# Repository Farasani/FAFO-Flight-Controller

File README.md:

# FAFO

<picture>
  <source media="(prefers-color-scheme: dark)" width=60% height=60% srcset="https://github.com/user-attachments/assets/f2668aae-5746-43aa-aec3-286b064c4626">
  <source media="(prefers-color-scheme: light)" width=60% height=60% srcset="https://github.com/user-attachments/assets/a5b0ae70-b65e-41dd-a281-93c37e5f3b0a">
  
</picture>

F4 Flight Controller for quadcopter, hecxacopter and fixed wings drones.

## Specs

- 168MHz STM32F405RGT6
- 5x UARTS serial ports
- I2C1
- 6-Axis ICM-42688-P
- MAX7456 OSD
- BMP280 Barometer
- 1GB BlackBox
- 6 PWM/DSHOT outputs

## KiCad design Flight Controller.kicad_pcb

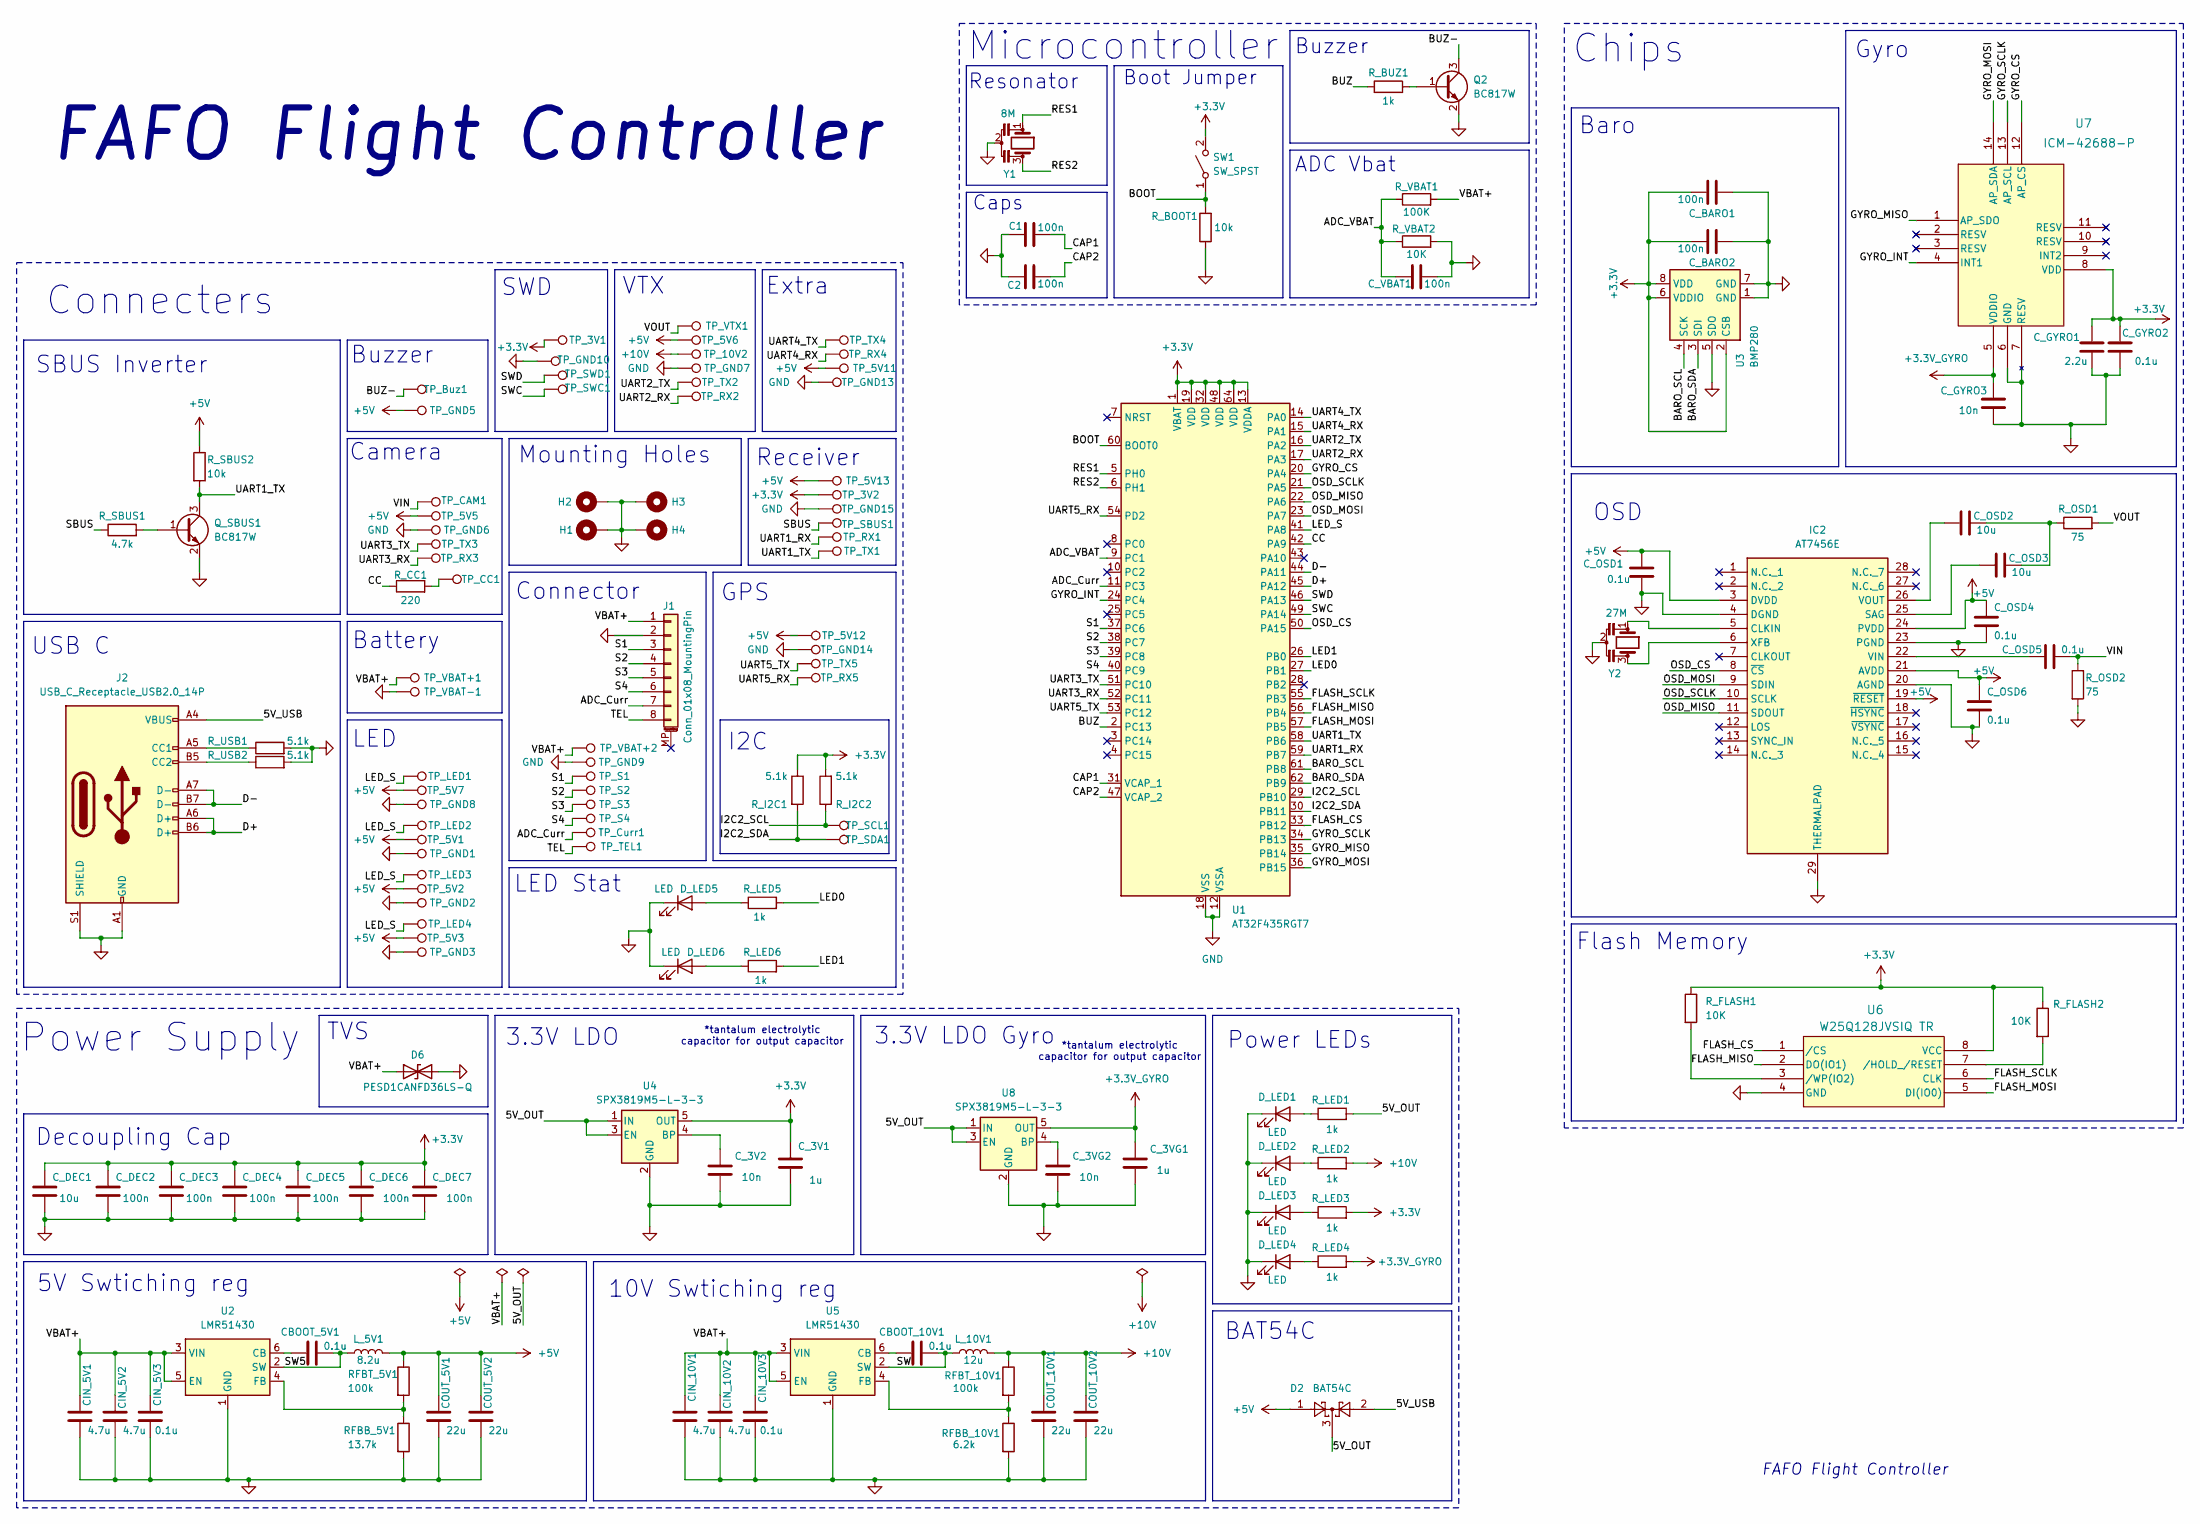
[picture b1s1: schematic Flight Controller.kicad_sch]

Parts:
C1, C2: 100n; C_0402_1005Metric
CBOOT_5V1, CBOOT_10V1: 0.1u; C_0603_1608Metric
CIN_5V1, CIN_5V2, CIN_10V1, CIN_10V2: 4.7u; C_0805_2012Metric
CIN_5V3, CIN_10V3: 0.1u; C_0402_1005Metric
COUT_5V1, COUT_5V2, COUT_10V1, COUT_10V2: 22u; C_0805_2012Metric
C_3V1, C_3VG1: 1u; C_0603_1608Metric
C_3V2, C_3VG2: 10n; C_0402_1005Metric
C_BARO1, C_BARO2: 100n; C_0402_1005Metric
C_DEC1: 10u; C_0603_1608Metric
C_DEC2, C_DEC3, C_DEC4, C_DEC5, C_DEC6, C_DEC7: 100n; C_0402_1005Metric
C_GYRO1: 2.2u; C_0402_1005Metric
C_GYRO2: 0.1u; C_0402_1005Metric
C_GYRO3: 10n; C_0402_1005Metric
C_OSD1, C_OSD4, C_OSD5, C_OSD6: 0.1u; C_0402_1005Metric
C_OSD2, C_OSD3: 10u; C_0402_1005Metric
C_VBAT1: 100n; C_0402_1005Metric
D2: BAT54C; SOT-23
D6: PESD1CANFD36LS-Q; D_SOD-882
D_LED1, D_LED2, D_LED3, D_LED4, D_LED5, D_LED6: LED; LED_0603_1608Metric
H1, H2, H3, H4: MountingHole_Pad; MountingHole_3.2mm_M3_DIN965_Pad
IC2: AT7456E; SOP65P637X110-28N; Manufacturer_Part_Number AT7456E
J1: Conn_01x08_MountingPin; JST_SH_SM08B-SRSS-TB_1x08-1MP_P1.00mm_Horizontal
J2: USB_C_Receptacle_USB2.0_14P; USB_C_Receptacle_GCT_USB4110
L_5V1: 8.2u; L_Vishay_IHLP-2525
L_10V1: 12u; 744393465120
Q2: BC817W; SOT-323_SC-70
Q_SBUS1: BC817W; SOT-323_SC-70
RFBB_5V1: 13.7k; R_0402_1005Metric
RFBB_10V1: 6.2k; R_0402_1005Metric
RFBT_5V1, RFBT_10V1: 100k; R_0402_1005Metric
R_BOOT1: 10k; R_0402_1005Metric
R_BUZ1: 1k; R_0402_1005Metric
R_CC1: 220; R_0402_1005Metric
R_FLASH1, R_FLASH2: 10K; R_0402_1005Metric
R_I2C1, R_I2C2: 5.1k; R_0402_1005Metric
R_LED1, R_LED2, R_LED3, R_LED4, R_LED5, R_LED6: 1k; R_0603_1608Metric
R_OSD1, R_OSD2: 75; R_0603_1608Metric
R_SBUS1: 4.7k; R_0805_2012Metric
R_SBUS2: 10k; R_0603_1608Metric
R_USB1, R_USB2: 5.1k; R_0603_1608Metric
R_VBAT1: 100K; R_0805_2012Metric
R_VBAT2: 10K; R_1206_3216Metric
SW1: SW_SPST; SW_SPST_EVQP2_MiddlePushTravel_H2.5mm
TP_3V1, TP_3V2, TP_5V1, TP_5V2, TP_5V3, TP_5V5, TP_5V6, TP_5V7, TP_5V11, TP_5V12, TP_5V13, TP_10V2: TestPoint; Solder_Pad_SMD
TP_Buz1: TestPoint; Solder_Pad_SMD
TP_CAM1: TestPoint; Solder_Pad_SMD
TP_CC1: TestPoint; Solder_Pad_SMD
TP_Curr1: TestPoint; Solder_Pad_SMD_Half
TP_GND1, TP_GND2, TP_GND3, TP_GND5, TP_GND6, TP_GND7, TP_GND8, TP_GND10, TP_GND13, TP_GND14, TP_GND15: TestPoint; Solder_Pad_SMD
TP_GND9: TestPoint; Solder_Pad_SMD_Half
TP_LED1, TP_LED2, TP_LED3, TP_LED4: TestPoint; Solder_Pad_SMD
TP_RX1, TP_RX2, TP_RX3, TP_RX4, TP_RX5: TestPoint; Solder_Pad_SMD
TP_S1, TP_S2, TP_S3, TP_S4: TestPoint; Solder_Pad_SMD_Half
TP_SBUS1: TestPoint; Solder_Pad_SMD
TP_SCL1: TestPoint; Solder_Pad_SMD
TP_SDA1: TestPoint; Solder_Pad_SMD
TP_SWC1: TestPoint; Solder_Pad_SMD
TP_SWD1: TestPoint; Solder_Pad_SMD
TP_TEL1: TestPoint; Solder_Pad_SMD_Half
TP_TX1, TP_TX2, TP_TX3, TP_TX4, TP_TX5: TestPoint; Solder_Pad_SMD
TP_VBAT+1: TestPoint; Solder_Pad_SMD
TP_VBAT+2: TestPoint; Solder_Pad_SMD_Half
TP_VBAT-1: TestPoint; Solder_Pad_SMD
TP_VTX1: TestPoint; Solder_Pad_SMD
U1: AT32F435RGT7; LQFP-64_10x10mm_P0.5mm
U2, U5: LMR51430; SOT-23-6
U3: BMP280; Bosch_LGA-8_2x2.5mm_P0.65mm_ClockwisePinNumbering
U4, U8: SPX3819M5-L-3-3; SOT-23-5
U6: W25Q128JVSIQ TR; SOIC_208MIL_WIN
U7: ICM-42688-P; Bosch_LGA-14_3x2.5mm_P0.5mm
Y1: 8M; Resonator_SMD_Murata_CSTxExxV-3Pin_3.0x1.1mm
Y2: 27M; E2X270061X04

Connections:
+3.3V: C_3V1.1, C_BARO1.2, C_BARO2.2, C_DEC1.1, C_DEC2.1, C_DEC3.1, C_DEC4.1, C_DEC5.1, C_DEC6.1, C_DEC7.1, C_GYRO1.1, C_GYRO2.1, R_FLASH1.1, R_FLASH2.1, R_I2C1.1, R_I2C2.2, R_LED3.2, SW1.2 (B), TP_3V1.1, TP_3V2.1, U1.1 (VBAT), U1.13 (VDDA), U1.19 (VDD), U1.32 (VDD), U1.48 (VDD), U1.64 (VDD), U3.2 (CSB), U3.6 (VDDIO), U3.8 (VDD), U4.5 (OUT), U6.8 (VCC), U7.8 (VDD)
+3.3V_GYRO: C_3VG1.1, C_GYRO3.1, R_LED4.2, U7.5 (VDDIO), U8.5 (OUT)
+5V: COUT_5V1.1, COUT_5V2.1, C_OSD1.1, C_OSD4.1, C_OSD6.1, D2.1, IC2.3 (DVDD), IC2.19 (~RESET), IC2.21 (AVDD), IC2.24 (PVDD), L_5V1.2, RFBT_5V1.1, R_SBUS2.1, TP_5V1.1, TP_5V2.1, TP_5V3.1, TP_5V5.1, TP_5V6.1, TP_5V7.1, TP_5V11.1, TP_5V12.1, TP_5V13.1, TP_GND5.1
+10V: COUT_10V1.1, COUT_10V2.1, L_10V1.2, RFBT_10V1.1, R_LED2.2, TP_10V2.1
/5V_OUT: D2.3, R_LED1.2, U4.1 (IN), U4.3 (EN), U8.1 (IN), U8.3 (EN)
/5V_USB: D2.2, J2.A4 (VBUS), J2.A9 (VBUS), J2.B4 (VBUS), J2.B9 (VBUS)
/ADC_Curr: J1.7, TP_Curr1.1, U1.11 (PC3)
/ADC_VBAT: C_VBAT1.2, R_VBAT1.1, R_VBAT2.1, U1.9 (PC1)
/BARO_SCL: U1.61 (PB8), U3.4 (SCK)
/BARO_SDA: U1.62 (PB9), U3.3 (SDI)
/BOOT: R_BOOT1.2, SW1.1 (A), U1.60 (BOOT0)
/BUZ: R_BUZ1.1, U1.2 (PC13)
/BUZ-: Q2.3 (C), TP_Buz1.1
/CAP1: C1.2, U1.31 (VCAP_1)
/CAP2: C2.2, U1.47 (VCAP_2)
/CC: R_CC1.1, U1.42 (PA9)
/D+: J2.A6 (D+), J2.B6 (D+), U1.45 (PA12)
/D-: J2.A7 (D-), J2.B7 (D-), U1.44 (PA11)
/FLASH_CS: U1.33 (PB12), U6.1 (/CS)
/FLASH_MISO: U1.56 (PB4), U6.2 (DO(IO1))
/FLASH_MOSI: U1.57 (PB5), U6.5 (DI(IO0))
/FLASH_SCLK: U1.55 (PB3), U6.6 (CLK)
/GYRO_CS: U1.20 (PA4), U7.12 (AP_CS)
/GYRO_INT: U1.24 (PC4), U7.4 (INT1)
/GYRO_MISO: U1.35 (PB14), U7.1 (AP_SDO)
/GYRO_MOSI: U1.36 (PB15), U7.14 (AP_SDA)
/GYRO_SCLK: U1.34 (PB13), U7.13 (AP_SCL)
/I2C2_SCL: R_I2C2.1, TP_SCL1.1, U1.29 (PB10)
/I2C2_SDA: R_I2C1.2, TP_SDA1.1, U1.30 (PB11)
/LED0: R_LED5.2, U1.27 (PB1)
/LED1: R_LED6.2, U1.26 (PB0)
/LED_S: TP_LED1.1, TP_LED2.1, TP_LED3.1, TP_LED4.1, U1.41 (PA8)
/OSD_CS: IC2.8 (~CS), U1.50 (PA15)
/OSD_MISO: IC2.11 (SDOUT), U1.22 (PA6)
/OSD_MOSI: IC2.9 (SDIN), U1.23 (PA7)
/OSD_SCLK: IC2.10 (SCLK), U1.21 (PA5)
/RES1: U1.5 (PH0), Y1.1
/RES2: U1.6 (PH1), Y1.3
/S1: J1.3, TP_S1.1, U1.37 (PC6)
/S2: J1.4, TP_S2.1, U1.38 (PC7)
/S3: J1.5, TP_S3.1, U1.39 (PC8)
/S4: J1.6, TP_S4.1, U1.40 (PC9)
/SBUS: R_SBUS1.1, TP_SBUS1.1
/SW: CBOOT_10V1.2, L_10V1.1, U5.2 (SW)
/SW5: CBOOT_5V1.2, L_5V1.1, U2.2 (SW)
/SWC: TP_SWC1.1, U1.49 (PA14)
/SWD: TP_SWD1.1, U1.46 (PA13)
/TEL: J1.8, TP_TEL1.1
/UART1_RX: TP_RX1.1, U1.59 (PB7)
/UART1_TX: Q_SBUS1.3 (C), R_SBUS2.2, TP_TX1.1, U1.58 (PB6)
/UART2_RX: TP_RX2.1, U1.17 (PA3)
/UART2_TX: TP_TX2.1, U1.16 (PA2)
/UART3_RX: TP_RX3.1, U1.52 (PC11)
/UART3_TX: TP_TX3.1, U1.51 (PC10)
/UART4_RX: TP_RX4.1, U1.15 (PA1)
/UART4_TX: TP_TX4.1, U1.14 (PA0)
/UART5_RX: TP_RX5.1, U1.54 (PD2)
/UART5_TX: TP_TX5.1, U1.53 (PC12)
/VBAT+: CIN_5V1.1, CIN_5V2.1, CIN_5V3.2, CIN_10V1.1, CIN_10V2.1, CIN_10V3.2, D6.1 (A1), J1.1, R_VBAT1.2, TP_VBAT+1.1, TP_VBAT+2.1, U2.3 (VIN), U2.5 (EN), U5.3 (VIN), U5.5 (EN)
/VIN: C_OSD5.2, R_OSD2.1, TP_CAM1.1
/VOUT: R_OSD1.2, TP_VTX1.1
GND: C1.1, C2.1, CIN_5V1.2, CIN_5V2.2, CIN_5V3.1, CIN_10V1.2, CIN_10V2.2, CIN_10V3.1, COUT_5V1.2, COUT_5V2.2, COUT_10V1.2, COUT_10V2.2, C_3V1.2, C_3V2.2, C_3VG1.2, C_3VG2.2, C_BARO1.1, C_BARO2.1, C_DEC1.2, C_DEC2.2, C_DEC3.2, C_DEC4.2, C_DEC5.2, C_DEC6.2, C_DEC7.2, C_GYRO1.2, C_GYRO2.2, C_GYRO3.2, C_OSD1.2, C_OSD4.2, C_OSD6.2, C_VBAT1.1, D6.2 (A2), D_LED1.1 (K), D_LED2.1 (K), D_LED3.1 (K), D_LED4.1 (K), D_LED5.1 (K), D_LED6.1 (K), H1.1, H2.1, H3.1, H4.1, IC2.4 (DGND), IC2.20 (AGND), IC2.23 (PGND), IC2.29 (THERMALPAD), J1.2, J2.A1 (GND), J2.A12 (GND), J2.B1 (GND), J2.B12 (GND), J2.S1 (SHIELD), Q2.2 (E), Q_SBUS1.2 (E), RFBB_5V1.2, RFBB_10V1.2, R_BOOT1.1, R_OSD2.2, R_USB1.2, R_USB2.2, R_VBAT2.2, TP_GND1.1, TP_GND2.1, TP_GND3.1, TP_GND6.1, TP_GND7.1, TP_GND8.1, TP_GND9.1, TP_GND10.1, TP_GND13.1, TP_GND14.1, TP_GND15.1, TP_VBAT-1.1, U1.12 (VSSA), U1.18 (VSS), U1.63 (VSS), U2.1 (GND), U3.1 (GND), U3.5 (SDO), U3.7 (GND), U4.2 (GND), U5.1 (GND), U6.4 (GND), U7.6 (GND), U7.7 (RESV), U8.2 (GND), Y1.2, Y2.2
unnamed: C_OSD2.2, C_OSD3.2, R_OSD1.1
unnamed: D_LED1.2 (A), R_LED1.1
unnamed: D_LED2.2 (A), R_LED2.1
unnamed: D_LED3.2 (A), R_LED3.1
unnamed: D_LED4.2 (A), R_LED4.1
unnamed: D_LED5.2 (A), R_LED5.1
unnamed: D_LED6.2 (A), R_LED6.1
unnamed: IC2.5 (CLKIN), Y2.1
unnamed: C_OSD3.1, IC2.25 (SAG)
unnamed: C_OSD5.1, IC2.22 (VIN)
unnamed: C_OSD2.1, IC2.26 (VOUT)
unnamed: IC2.6 (XFB), Y2.3
unnamed: J2.A5 (CC1), R_USB1.1
unnamed: J2.B5 (CC2), R_USB2.1
unnamed: Q2.1 (B), R_BUZ1.2
unnamed: Q_SBUS1.1 (B), R_SBUS1.2
unnamed: R_CC1.2, TP_CC1.1
unnamed: CBOOT_5V1.1, U2.6 (CB)
unnamed: RFBB_5V1.1, RFBT_5V1.2, U2.4 (FB)
unnamed: C_3V2.1, U4.4 (BP)
unnamed: CBOOT_10V1.1, U5.6 (CB)
unnamed: RFBB_10V1.1, RFBT_10V1.2, U5.4 (FB)
unnamed: R_FLASH2.2, U6.7 (/HOLD_/RESET)
unnamed: R_FLASH1.2, U6.3 (/WP(IO2))
unnamed: C_3VG2.1, U8.4 (BP)

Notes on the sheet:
LED
Receiver
SBUS Inverter
Buzzer
Extra
FAFO Flight Controller
Battery
SWD
*tantalum electrolytic capacitor for output capacitor
Resonator
Decoupling Cap
Mounting Holes
3.3V LDO Gyro
Camera
Baro
Gyro
3.3V LDO
Caps
Microcontroller
Flash Memory
GPS
USB C
10V Swtiching reg
I2C
TVS
Power LEDs
Connector
BAT54C
VTX
Power Supply
Boot Jumper
LED Stat
ADC Vbat
5V Swtiching reg
OSD
Connecters
Chips

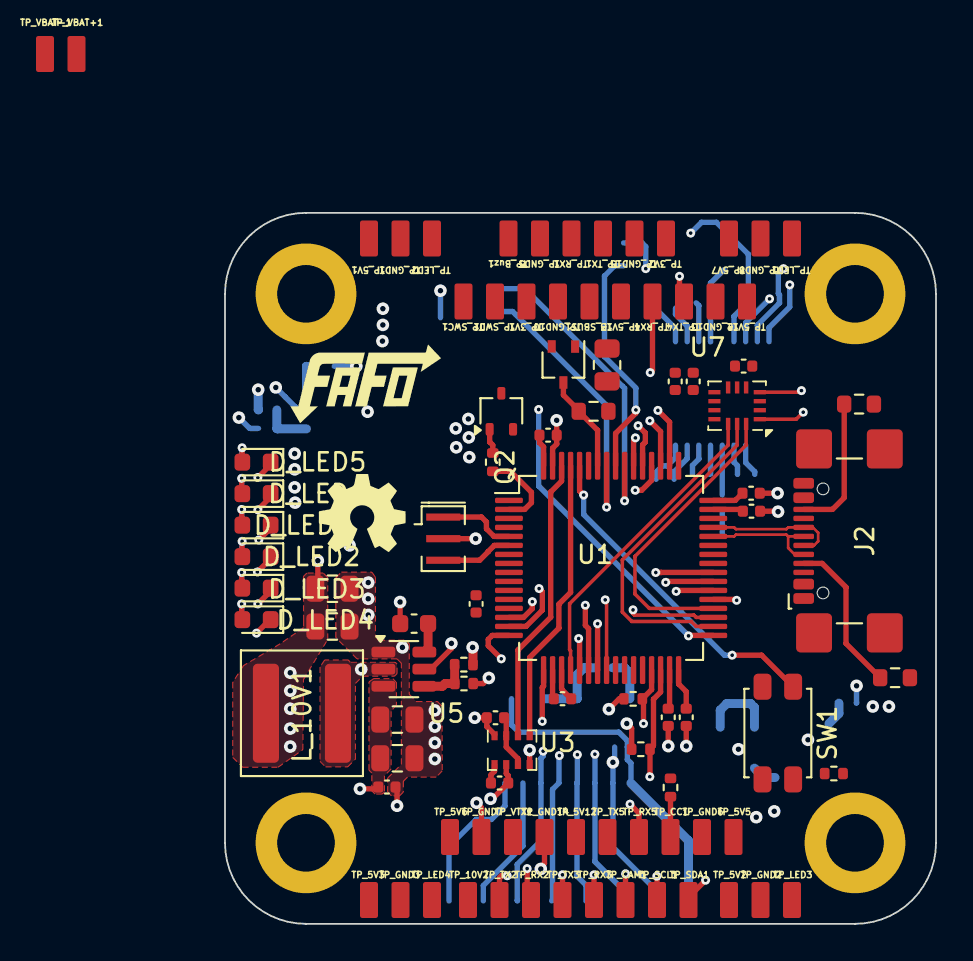
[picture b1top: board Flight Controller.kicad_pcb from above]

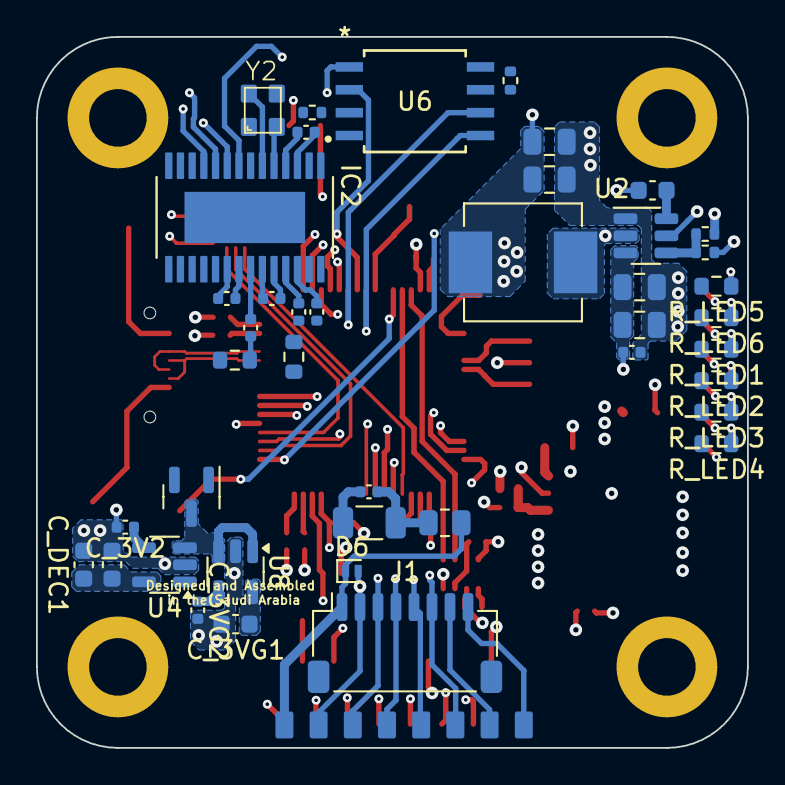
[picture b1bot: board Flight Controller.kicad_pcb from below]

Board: 6 copper layers, 39.5 x 39.5 mm, 147 parts (50 on the bottom side), 87 nets.

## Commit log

2024-04-01 added Kicad files
2024-04-08 schematic update
2024-04-08 pdf upload
2024-04-16 Update Schematic
2024-08-04 Updated Schematics
2025-01-04 Finshed Schematics and started with layout
2025-08-17 Readme
2025-08-21 Layout Update
2025-08-25 Power Supply Sch Udpate
2025-08-30 Changes to compline with Betaflighe guidlines
2025-09-08 assgining new pins
2025-09-09 Power Supply Updates
2025-09-10 New connectors
2025-09-18 I hope I'm done here with the sch
2025-09-18 This time I'm done fr
2025-09-18 I'm losing it
2025-09-19 Updated naming system
2025-09-19 I'm losing it again
2025-09-20 AHHHHHHHHHHHH
2025-09-20 One day this will be over
2025-09-20 Footprint Assignment Done
2025-09-20 Updated Layout
2025-09-21 First Layout
2025-09-25 Changed LDOs
2025-09-25 Routing
2025-09-26 Layout Updates
2025-10-20 We are going 6 layers BABYYgit add --all!
2025-10-24 Power Supply Layout
2025-10-25 Layout
2026-01-10 Test
